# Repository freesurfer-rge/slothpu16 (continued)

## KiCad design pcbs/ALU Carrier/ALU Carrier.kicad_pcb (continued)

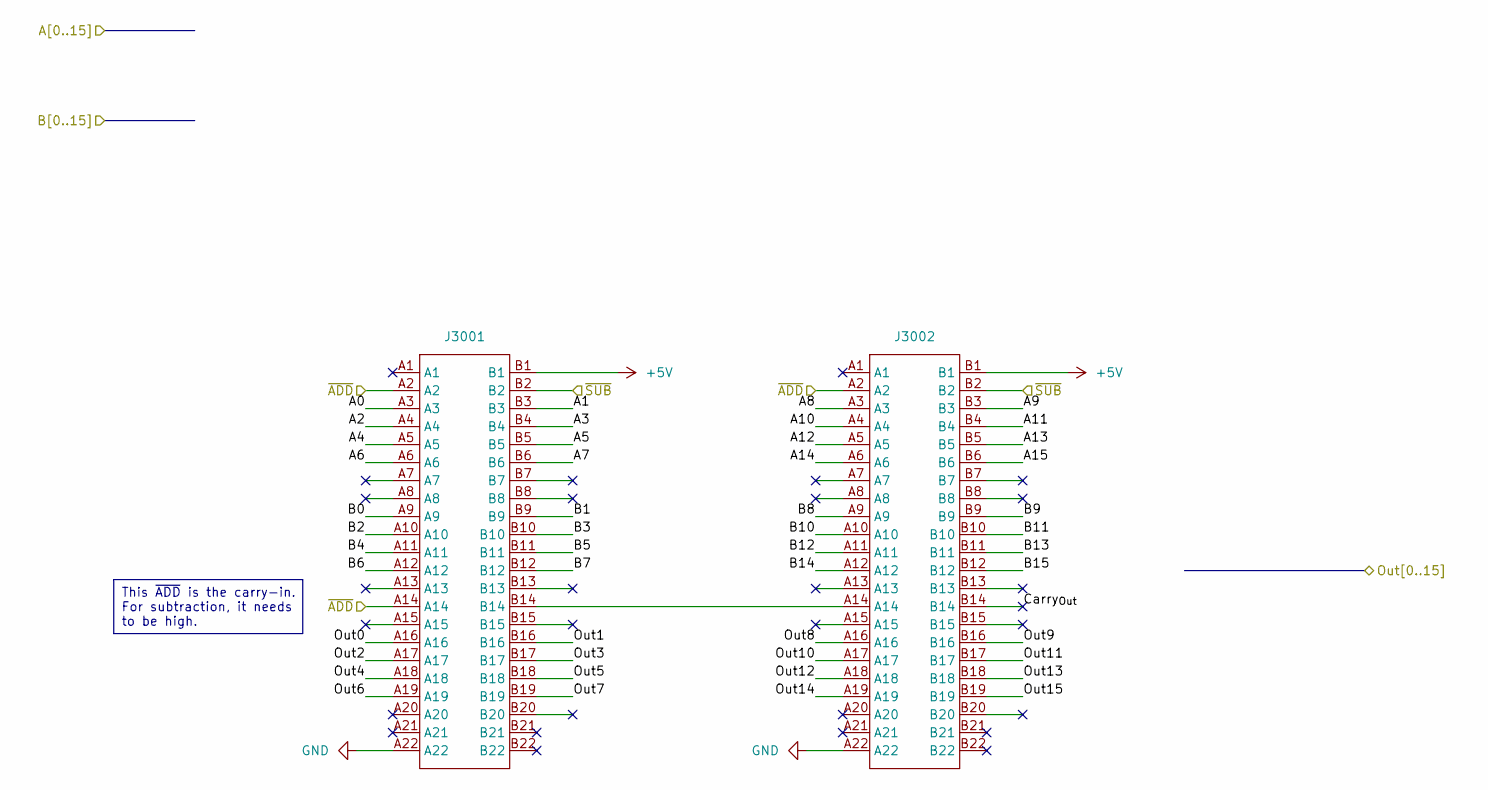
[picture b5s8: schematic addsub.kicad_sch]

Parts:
J3001, J3002: TE-5530843-4-Mount

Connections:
+5V: J3001.B1, J3002.B1; also elsewhere on the board
/A0: J3001.A3; also elsewhere on the board
/A1: J3001.B3; also elsewhere on the board
/A2: J3001.A4; also elsewhere on the board
/A3: J3001.B4; also elsewhere on the board
/A4: J3001.A5; also elsewhere on the board
/A5: J3001.B5; also elsewhere on the board
/A6: J3001.A6; also elsewhere on the board
/A7: J3001.B6; also elsewhere on the board
/A8: J3002.A3; also elsewhere on the board
/A9: J3002.B3; also elsewhere on the board
/A10: J3002.A4; also elsewhere on the board
/A11: J3002.B4; also elsewhere on the board
/A12: J3002.A5; also elsewhere on the board
/A13: J3002.B5; also elsewhere on the board
/A14: J3002.A6; also elsewhere on the board
/A15: J3002.B6; also elsewhere on the board
/Adder Subtractor/Carry_{Out}: J3002.B14
/Adder Subtractor/Out0: J3001.A16; also elsewhere on the board
/Adder Subtractor/Out1: J3001.B16; also elsewhere on the board
/Adder Subtractor/Out2: J3001.A17; also elsewhere on the board
/Adder Subtractor/Out3: J3001.B17; also elsewhere on the board
/Adder Subtractor/Out4: J3001.A18; also elsewhere on the board
/Adder Subtractor/Out5: J3001.B18; also elsewhere on the board
/Adder Subtractor/Out6: J3001.A19; also elsewhere on the board
/Adder Subtractor/Out7: J3001.B19; also elsewhere on the board
/Adder Subtractor/Out8: J3002.A16; also elsewhere on the board
/Adder Subtractor/Out9: J3002.B16; also elsewhere on the board
/Adder Subtractor/Out10: J3002.A17; also elsewhere on the board
/Adder Subtractor/Out11: J3002.B17; also elsewhere on the board
/Adder Subtractor/Out12: J3002.A18; also elsewhere on the board
/Adder Subtractor/Out13: J3002.B18; also elsewhere on the board
/Adder Subtractor/Out14: J3002.A19; also elsewhere on the board
/Adder Subtractor/Out15: J3002.B19; also elsewhere on the board
/Adder Subtractor/~ADD: J3001.A2, J3001.A14, J3002.A2; also elsewhere on the board
/Adder Subtractor/~SUB: J3001.B2, J3002.B2; also elsewhere on the board
/B0: J3001.A9; also elsewhere on the board
/B1: J3001.B9; also elsewhere on the board
/B2: J3001.A10; also elsewhere on the board
/B3: J3001.B10; also elsewhere on the board
/B4: J3001.A11; also elsewhere on the board
/B5: J3001.B11; also elsewhere on the board
/B6: J3001.A12; also elsewhere on the board
/B7: J3001.B12; also elsewhere on the board
/B8: J3002.A9; also elsewhere on the board
/B9: J3002.B9; also elsewhere on the board
/B10: J3002.A10; also elsewhere on the board
/B11: J3002.B10; also elsewhere on the board
/B12: J3002.A11; also elsewhere on the board
/B13: J3002.B11; also elsewhere on the board
/B14: J3002.A12; also elsewhere on the board
/B15: J3002.B12; also elsewhere on the board
GND: J3001.A22, J3002.A22; also elsewhere on the board
unnamed: J3001.B14, J3002.A14

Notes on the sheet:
This ~{ADD} is the carry-in. For subtraction, it needs to be high.

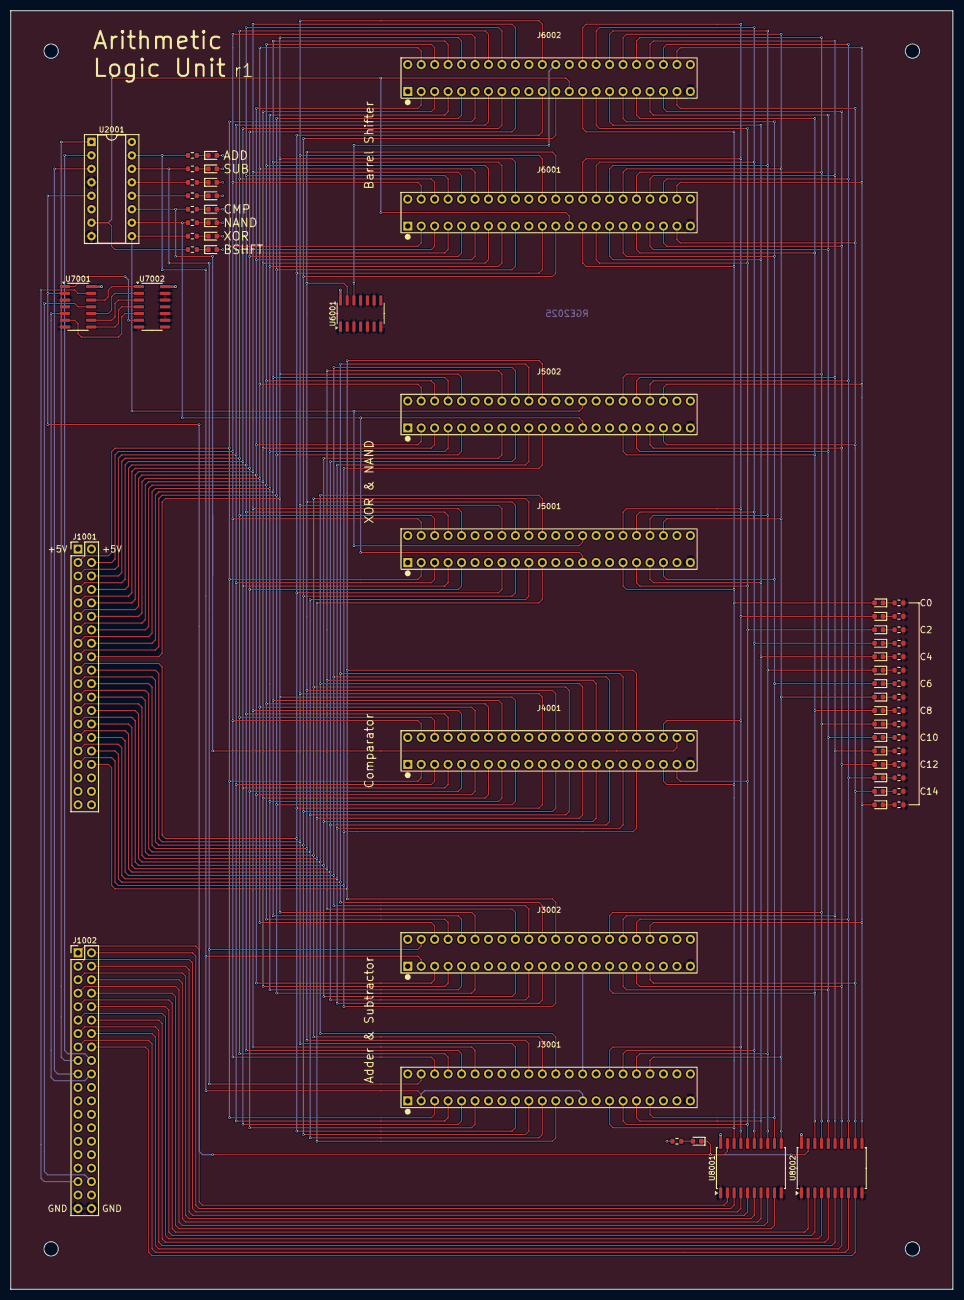
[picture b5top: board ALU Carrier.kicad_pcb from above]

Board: 2 copper layers, 177.8 x 241.3 mm, 69 parts (0 on the bottom side), 114 nets.

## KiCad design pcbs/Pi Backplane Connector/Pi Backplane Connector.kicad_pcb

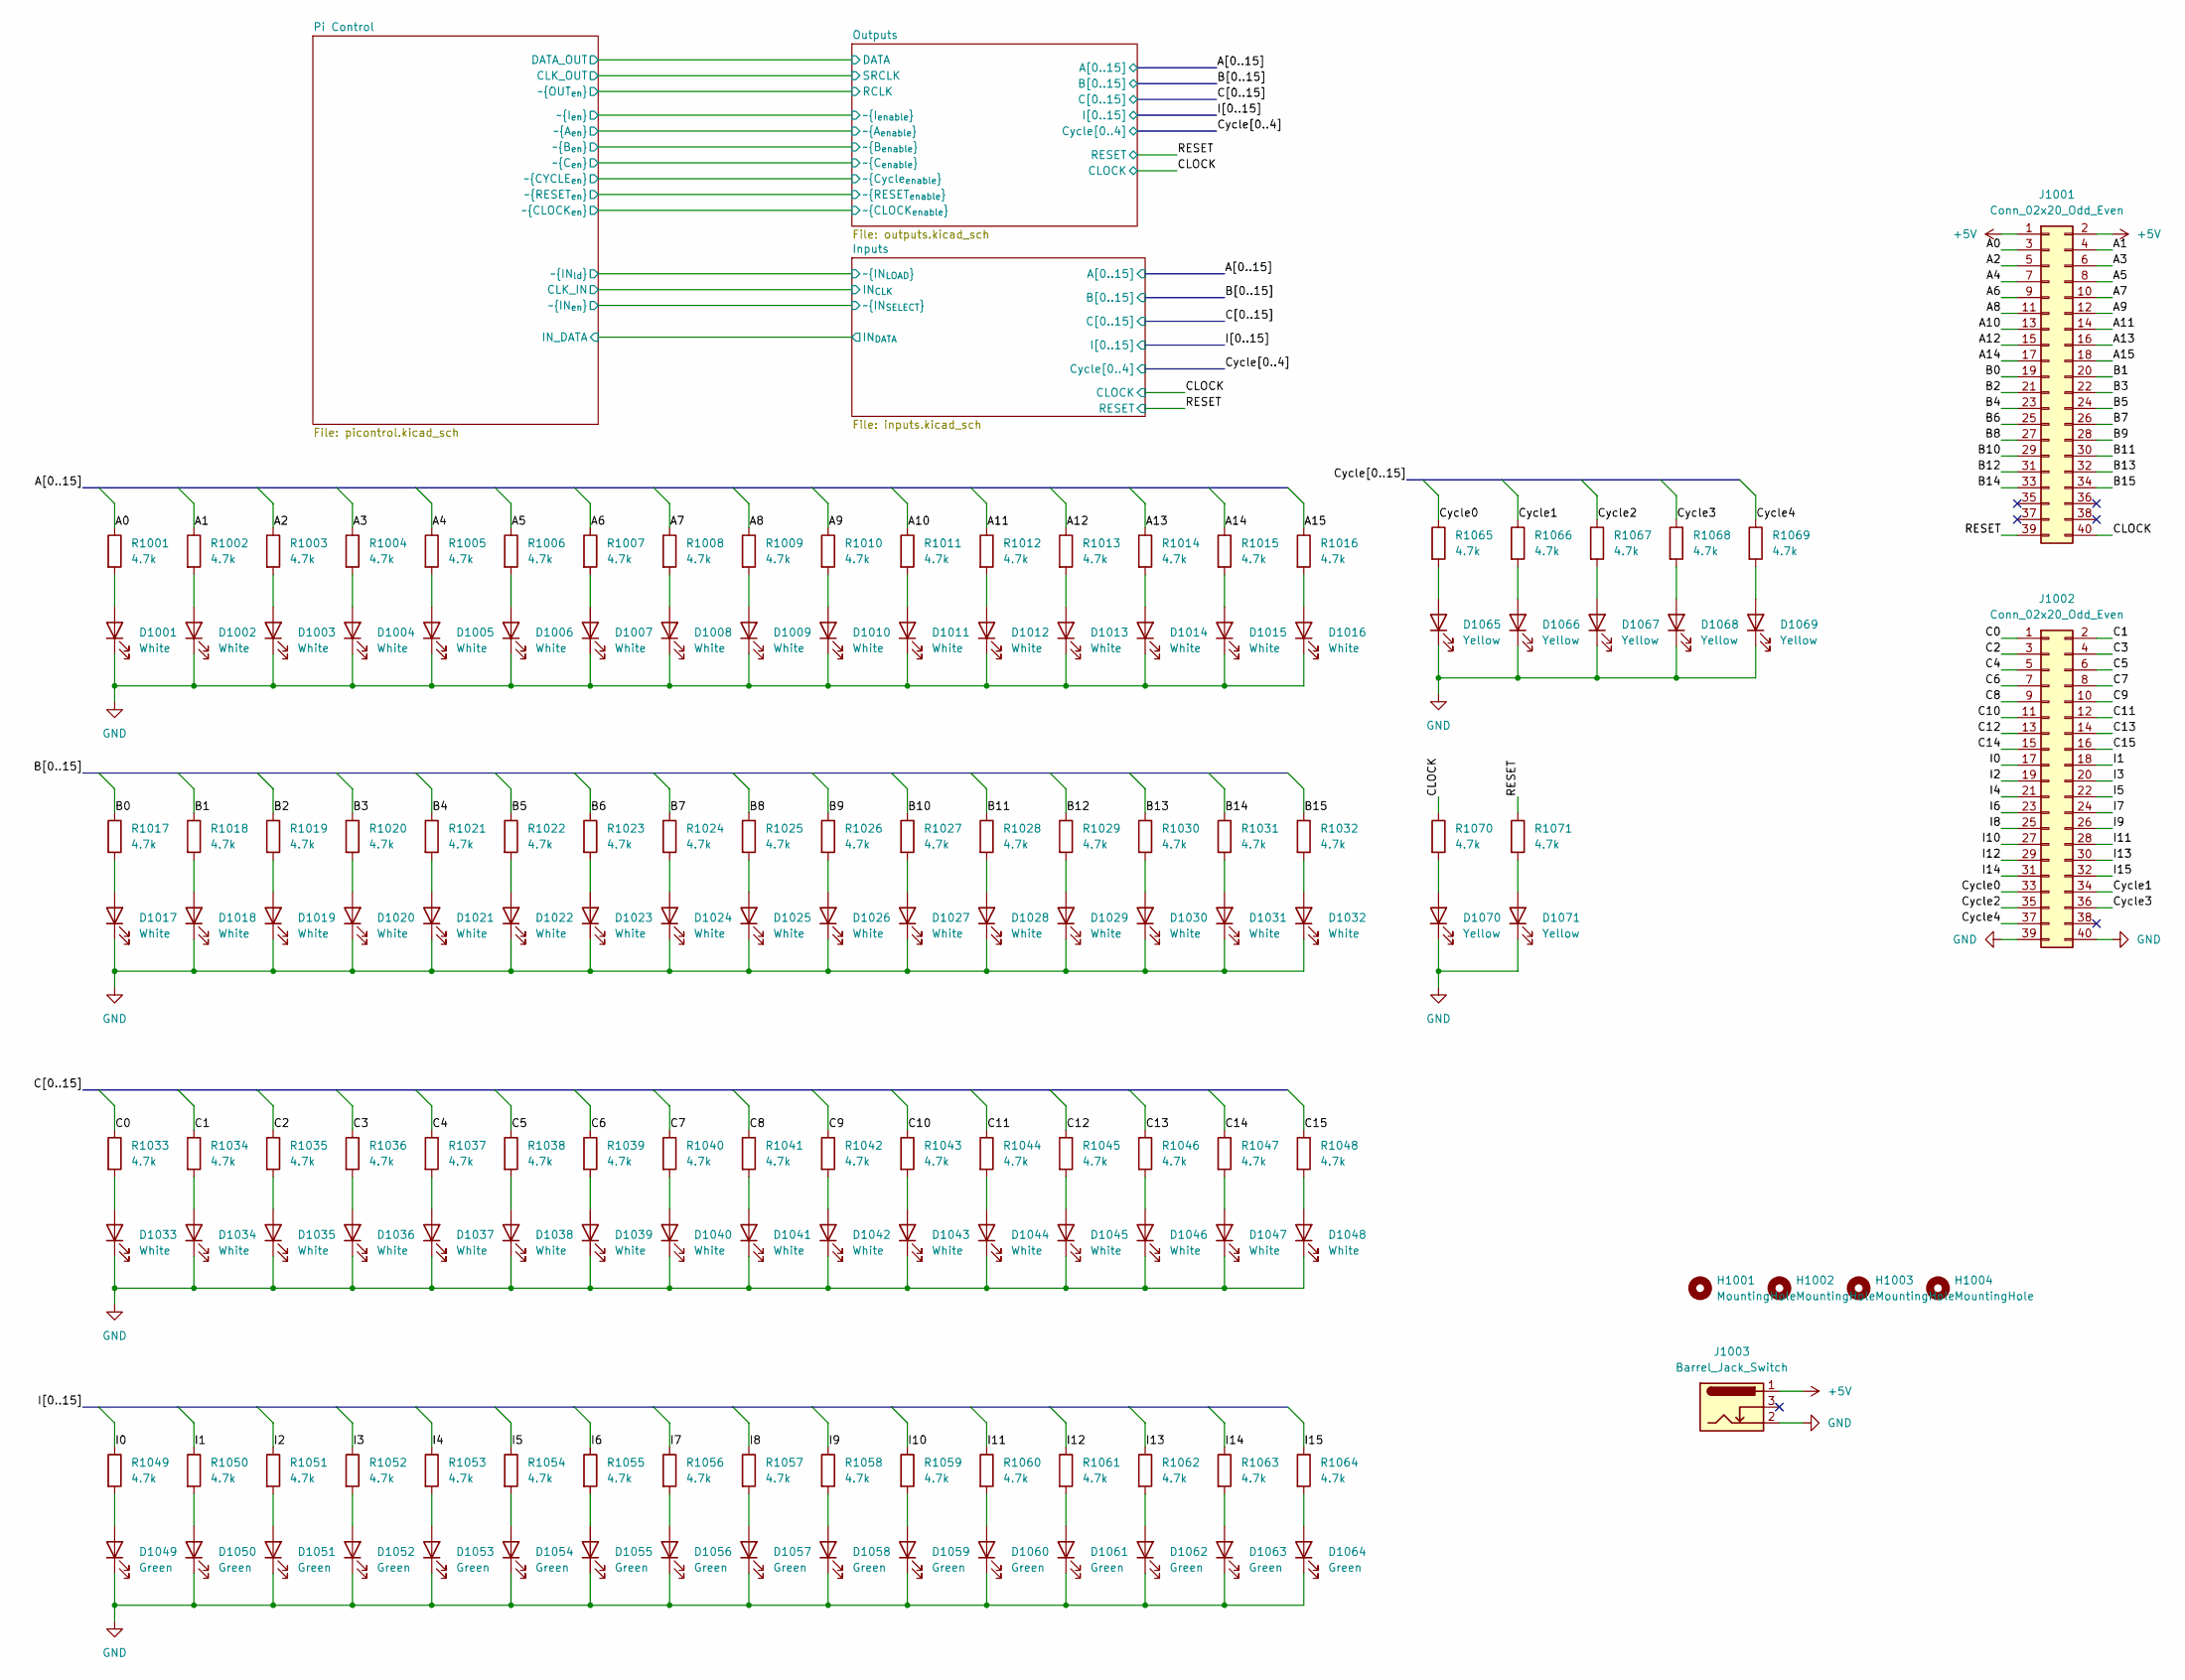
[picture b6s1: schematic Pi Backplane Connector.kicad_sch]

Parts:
D1001, D1002, D1003, D1004, D1005, D1006, D1007, D1008, D1009, D1010, D1011, D1012, D1013, D1014, D1015, D1016, D1017, D1018, D1019, D1020, D1021, D1022, D1023, D1024, D1025, D1026, D1027, D1028, D1029, D1030, D1031, D1032, D1033, D1034, D1035, D1036, D1037, D1038, D1039, D1040, D1041, D1042, D1043, D1044, D1045, D1046, D1047, D1048: White; LED_0603_1608Metric; LCSC C2290
D1049, D1050, D1051, D1052, D1053, D1054, D1055, D1056, D1057, D1058, D1059, D1060, D1061, D1062, D1063, D1064: Green; LED_0603_1608Metric; LCSC C72043
D1065, D1066, D1067, D1068, D1069, D1070, D1071: Yellow; LED_0603_1608Metric; LCSC C72038
H1001, H1002, H1003, H1004: MountingHole; MountingHole_2.7mm_M2.5_ISO7380
J1001, J1002: Conn_02x20_Odd_Even; PinHeader_2x20_P2.54mm_Vertical
J1003: Barrel_Jack_Switch; BarrelJack_Horizontal
R1001, R1002, R1003, R1004, R1005, R1006, R1007, R1008, R1009, R1010, R1011, R1012, R1013, R1014, R1015, R1016, R1017, R1018, R1019, R1020, R1021, R1022, R1023, R1024, R1025, R1026, R1027, R1028, R1029, R1030, R1031, R1032, R1033, R1034, R1035, R1036, R1037, R1038, R1039, R1040, R1041, R1042, R1043, R1044, R1045, R1046, R1047, R1048, R1049, R1050, R1051, R1052, R1053, R1054, R1055, R1056, R1057, R1058, R1059, R1060, R1061, R1062, R1063, R1064, R1065, R1066, R1067, R1068, R1069, R1070, R1071: 4.7k; R_0603_1608Metric; LCSC C23162

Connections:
+5V: J1001.1, J1001.2, J1003.1; also elsewhere on the board
/A0: J1001.3, R1001.1; also elsewhere on the board
/A1: J1001.4, R1002.1; also elsewhere on the board
/A2: J1001.5, R1003.1; also elsewhere on the board
/A3: J1001.6, R1004.1; also elsewhere on the board
/A4: J1001.7, R1005.1; also elsewhere on the board
/A5: J1001.8, R1006.1; also elsewhere on the board
/A6: J1001.9, R1007.1; also elsewhere on the board
/A7: J1001.10, R1008.1; also elsewhere on the board
/A8: J1001.11, R1009.1; also elsewhere on the board
/A9: J1001.12, R1010.1; also elsewhere on the board
/A10: J1001.13, R1011.1; also elsewhere on the board
/A11: J1001.14, R1012.1; also elsewhere on the board
/A12: J1001.15, R1013.1; also elsewhere on the board
/A13: J1001.16, R1014.1; also elsewhere on the board
/A14: J1001.17, R1015.1; also elsewhere on the board
/A15: J1001.18, R1016.1; also elsewhere on the board
/B0: J1001.19, R1017.1; also elsewhere on the board
/B1: J1001.20, R1018.1; also elsewhere on the board
/B2: J1001.21, R1019.1; also elsewhere on the board
/B3: J1001.22, R1020.1; also elsewhere on the board
/B4: J1001.23, R1021.1; also elsewhere on the board
/B5: J1001.24, R1022.1; also elsewhere on the board
/B6: J1001.25, R1023.1; also elsewhere on the board
/B7: J1001.26, R1024.1; also elsewhere on the board
/B8: J1001.27, R1025.1; also elsewhere on the board
/B9: J1001.28, R1026.1; also elsewhere on the board
/B10: J1001.29, R1027.1; also elsewhere on the board
/B11: J1001.30, R1028.1; also elsewhere on the board
/B12: J1001.31, R1029.1; also elsewhere on the board
/B13: J1001.32, R1030.1; also elsewhere on the board
/B14: J1001.33, R1031.1; also elsewhere on the board
/B15: J1001.34, R1032.1; also elsewhere on the board
/C0: J1002.1, R1033.1; also elsewhere on the board
/C1: J1002.2, R1034.1; also elsewhere on the board
/C2: J1002.3, R1035.1; also elsewhere on the board
/C3: J1002.4, R1036.1; also elsewhere on the board
/C4: J1002.5, R1037.1; also elsewhere on the board
/C5: J1002.6, R1038.1; also elsewhere on the board
/C6: J1002.7, R1039.1; also elsewhere on the board
/C7: J1002.8, R1040.1; also elsewhere on the board
/C8: J1002.9, R1041.1; also elsewhere on the board
/C9: J1002.10, R1042.1; also elsewhere on the board
/C10: J1002.11, R1043.1; also elsewhere on the board
/C11: J1002.12, R1044.1; also elsewhere on the board
/C12: J1002.13, R1045.1; also elsewhere on the board
/C13: J1002.14, R1046.1; also elsewhere on the board
/C14: J1002.15, R1047.1; also elsewhere on the board
/C15: J1002.16, R1048.1; also elsewhere on the board
/CLOCK: J1001.40, R1070.1; also elsewhere on the board
/Cycle0: J1002.33, R1065.1; also elsewhere on the board
/Cycle1: J1002.34, R1066.1; also elsewhere on the board
/Cycle2: J1002.35, R1067.1; also elsewhere on the board
/Cycle3: J1002.36, R1068.1; also elsewhere on the board
/Cycle4: J1002.37, R1069.1; also elsewhere on the board
/I0: J1002.17, R1049.1; also elsewhere on the board
/I1: J1002.18, R1050.1; also elsewhere on the board
/I2: J1002.19, R1051.1; also elsewhere on the board
/I3: J1002.20, R1052.1; also elsewhere on the board
/I4: J1002.21, R1053.1; also elsewhere on the board
/I5: J1002.22, R1054.1; also elsewhere on the board
/I6: J1002.23, R1055.1; also elsewhere on the board
/I7: J1002.24, R1056.1; also elsewhere on the board
/I8: J1002.25, R1057.1; also elsewhere on the board
/I9: J1002.26, R1058.1; also elsewhere on the board
/I10: J1002.27, R1059.1; also elsewhere on the board
/I11: J1002.28, R1060.1; also elsewhere on the board
/I12: J1002.29, R1061.1; also elsewhere on the board
/I13: J1002.30, R1062.1; also elsewhere on the board
/I14: J1002.31, R1063.1; also elsewhere on the board
/I15: J1002.32, R1064.1; also elsewhere on the board
/RESET: J1001.39, R1071.1; also elsewhere on the board
GND: D1001.1 (K), D1002.1 (K), D1003.1 (K), D1004.1 (K), D1005.1 (K), D1006.1 (K), D1007.1 (K), D1008.1 (K), D1009.1 (K), D1010.1 (K), D1011.1 (K), D1012.1 (K), D1013.1 (K), D1014.1 (K), D1015.1 (K), D1016.1 (K), D1017.1 (K), D1018.1 (K), D1019.1 (K), D1020.1 (K), D1021.1 (K), D1022.1 (K), D1023.1 (K), D1024.1 (K), D1025.1 (K), D1026.1 (K), D1027.1 (K), D1028.1 (K), D1029.1 (K), D1030.1 (K), D1031.1 (K), D1032.1 (K), D1033.1 (K), D1034.1 (K), D1035.1 (K), D1036.1 (K), D1037.1 (K), D1038.1 (K), D1039.1 (K), D1040.1 (K), D1041.1 (K), D1042.1 (K), D1043.1 (K), D1044.1 (K), D1045.1 (K), D1046.1 (K), D1047.1 (K), D1048.1 (K), D1049.1 (K), D1050.1 (K), D1051.1 (K), D1052.1 (K), D1053.1 (K), D1054.1 (K), D1055.1 (K), D1056.1 (K), D1057.1 (K), D1058.1 (K), D1059.1 (K), D1060.1 (K), D1061.1 (K), D1062.1 (K), D1063.1 (K), D1064.1 (K), D1065.1 (K), D1066.1 (K), D1067.1 (K), D1068.1 (K), D1069.1 (K), D1070.1 (K), D1071.1 (K), J1002.39, J1002.40, J1003.2; also elsewhere on the board
unnamed: D1001.2 (A), R1001.2
unnamed: D1002.2 (A), R1002.2
unnamed: D1003.2 (A), R1003.2
unnamed: D1004.2 (A), R1004.2
unnamed: D1005.2 (A), R1005.2
unnamed: D1006.2 (A), R1006.2
unnamed: D1007.2 (A), R1007.2
unnamed: D1008.2 (A), R1008.2
unnamed: D1009.2 (A), R1009.2
unnamed: D1010.2 (A), R1010.2
unnamed: D1011.2 (A), R1011.2
unnamed: D1012.2 (A), R1012.2
unnamed: D1013.2 (A), R1013.2
unnamed: D1014.2 (A), R1014.2
unnamed: D1015.2 (A), R1015.2
unnamed: D1016.2 (A), R1016.2
unnamed: D1017.2 (A), R1017.2
unnamed: D1018.2 (A), R1018.2
unnamed: D1019.2 (A), R1019.2
unnamed: D1020.2 (A), R1020.2
unnamed: D1021.2 (A), R1021.2
unnamed: D1022.2 (A), R1022.2
unnamed: D1023.2 (A), R1023.2
unnamed: D1024.2 (A), R1024.2
unnamed: D1025.2 (A), R1025.2
unnamed: D1026.2 (A), R1026.2
unnamed: D1027.2 (A), R1027.2
unnamed: D1028.2 (A), R1028.2
unnamed: D1029.2 (A), R1029.2
unnamed: D1030.2 (A), R1030.2
unnamed: D1031.2 (A), R1031.2
unnamed: D1032.2 (A), R1032.2
unnamed: D1033.2 (A), R1033.2
unnamed: D1034.2 (A), R1034.2
unnamed: D1035.2 (A), R1035.2
unnamed: D1036.2 (A), R1036.2
unnamed: D1037.2 (A), R1037.2
unnamed: D1038.2 (A), R1038.2
unnamed: D1039.2 (A), R1039.2
unnamed: D1040.2 (A), R1040.2
unnamed: D1041.2 (A), R1041.2
unnamed: D1042.2 (A), R1042.2
unnamed: D1043.2 (A), R1043.2
unnamed: D1044.2 (A), R1044.2
unnamed: D1045.2 (A), R1045.2
unnamed: D1046.2 (A), R1046.2
unnamed: D1047.2 (A), R1047.2
unnamed: D1048.2 (A), R1048.2
unnamed: D1049.2 (A), R1049.2
unnamed: D1050.2 (A), R1050.2
unnamed: D1051.2 (A), R1051.2
unnamed: D1052.2 (A), R1052.2
unnamed: D1053.2 (A), R1053.2
unnamed: D1054.2 (A), R1054.2
unnamed: D1055.2 (A), R1055.2
unnamed: D1056.2 (A), R1056.2
unnamed: D1057.2 (A), R1057.2
unnamed: D1058.2 (A), R1058.2
unnamed: D1059.2 (A), R1059.2
unnamed: D1060.2 (A), R1060.2
unnamed: D1061.2 (A), R1061.2
unnamed: D1062.2 (A), R1062.2
unnamed: D1063.2 (A), R1063.2
unnamed: D1064.2 (A), R1064.2
unnamed: D1065.2 (A), R1065.2
unnamed: D1066.2 (A), R1066.2
unnamed: D1067.2 (A), R1067.2
unnamed: D1068.2 (A), R1068.2
unnamed: D1069.2 (A), R1069.2
unnamed: D1070.2 (A), R1070.2
unnamed: D1071.2 (A), R1071.2

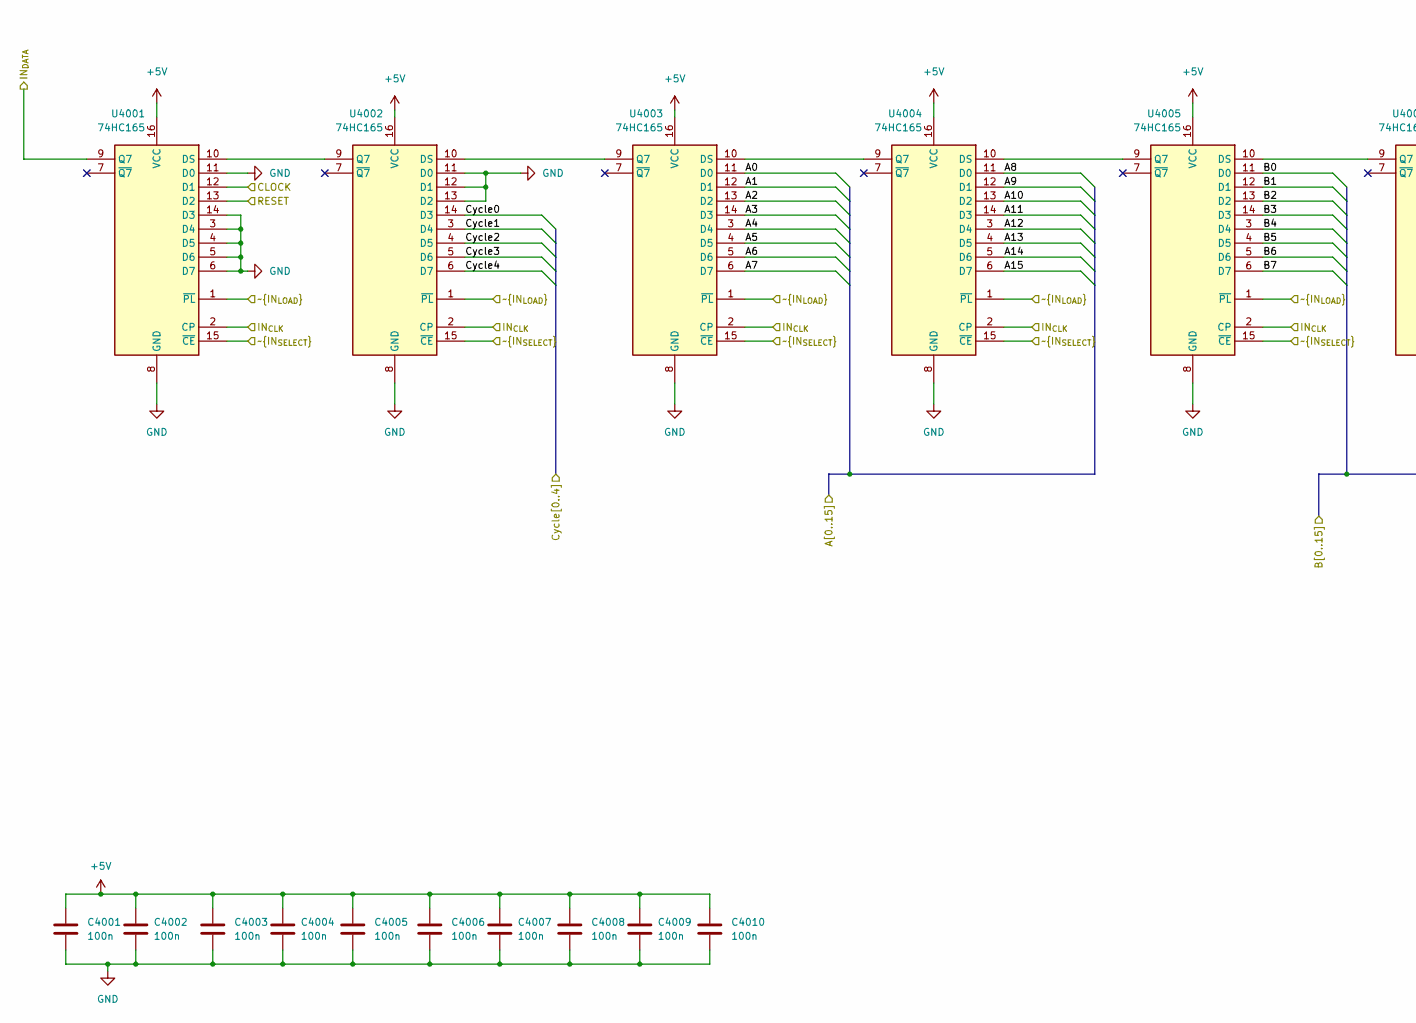
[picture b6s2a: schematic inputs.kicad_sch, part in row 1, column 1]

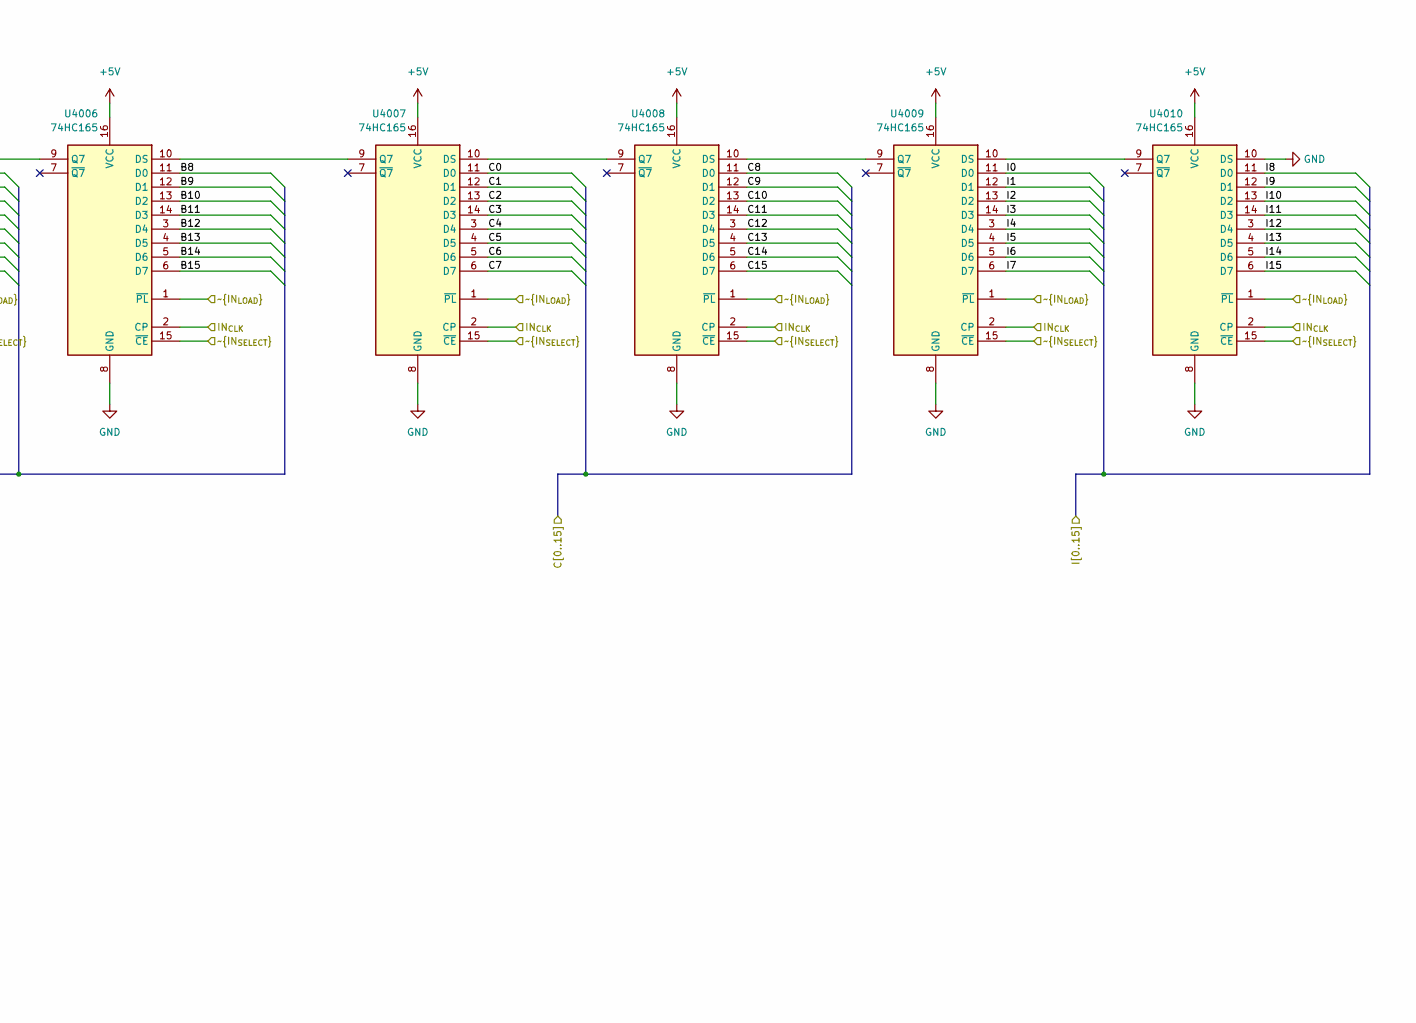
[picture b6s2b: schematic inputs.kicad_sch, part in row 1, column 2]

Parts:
C4001, C4002, C4003, C4004, C4005, C4006, C4007, C4008, C4009, C4010: 100n; C_0603_1608Metric; LCSC C14663
U4001, U4002, U4003, U4004, U4005, U4006, U4007, U4008, U4009, U4010: 74HC165; SOIC-16_3.9x9.9mm_P1.27mm; LCSC C5613

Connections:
+5V: C4001.2, C4002.2, C4003.2, C4004.2, C4005.2, C4006.2, C4007.2, C4008.2, C4009.2, C4010.2, U4001.16 (VCC), U4002.16 (VCC), U4003.16 (VCC), U4004.16 (VCC), U4005.16 (VCC), U4006.16 (VCC), U4007.16 (VCC), U4008.16 (VCC), U4009.16 (VCC), U4010.16 (VCC); also elsewhere on the board
/A0: U4003.11 (D0); also elsewhere on the board
/A1: U4003.12 (D1); also elsewhere on the board
/A2: U4003.13 (D2); also elsewhere on the board
/A3: U4003.14 (D3); also elsewhere on the board
/A4: U4003.3 (D4); also elsewhere on the board
/A5: U4003.4 (D5); also elsewhere on the board
/A6: U4003.5 (D6); also elsewhere on the board
/A7: U4003.6 (D7); also elsewhere on the board
/A8: U4004.11 (D0); also elsewhere on the board
/A9: U4004.12 (D1); also elsewhere on the board
/A10: U4004.13 (D2); also elsewhere on the board
/A11: U4004.14 (D3); also elsewhere on the board
/A12: U4004.3 (D4); also elsewhere on the board
/A13: U4004.4 (D5); also elsewhere on the board
/A14: U4004.5 (D6); also elsewhere on the board
/A15: U4004.6 (D7); also elsewhere on the board
/B0: U4005.11 (D0); also elsewhere on the board
/B1: U4005.12 (D1); also elsewhere on the board
/B2: U4005.13 (D2); also elsewhere on the board
/B3: U4005.14 (D3); also elsewhere on the board
/B4: U4005.3 (D4); also elsewhere on the board
/B5: U4005.4 (D5); also elsewhere on the board
/B6: U4005.5 (D6); also elsewhere on the board
/B7: U4005.6 (D7); also elsewhere on the board
/B8: U4006.11 (D0); also elsewhere on the board
/B9: U4006.12 (D1); also elsewhere on the board
/B10: U4006.13 (D2); also elsewhere on the board
/B11: U4006.14 (D3); also elsewhere on the board
/B12: U4006.3 (D4); also elsewhere on the board
/B13: U4006.4 (D5); also elsewhere on the board
/B14: U4006.5 (D6); also elsewhere on the board
/B15: U4006.6 (D7); also elsewhere on the board
/C0: U4007.11 (D0); also elsewhere on the board
/C1: U4007.12 (D1); also elsewhere on the board
/C2: U4007.13 (D2); also elsewhere on the board
/C3: U4007.14 (D3); also elsewhere on the board
/C4: U4007.3 (D4); also elsewhere on the board
/C5: U4007.4 (D5); also elsewhere on the board
/C6: U4007.5 (D6); also elsewhere on the board
/C7: U4007.6 (D7); also elsewhere on the board
/C8: U4008.11 (D0); also elsewhere on the board
/C9: U4008.12 (D1); also elsewhere on the board
/C10: U4008.13 (D2); also elsewhere on the board
/C11: U4008.14 (D3); also elsewhere on the board
/C12: U4008.3 (D4); also elsewhere on the board
/C13: U4008.4 (D5); also elsewhere on the board
/C14: U4008.5 (D6); also elsewhere on the board
/C15: U4008.6 (D7); also elsewhere on the board
/CLOCK: U4001.12 (D1); also elsewhere on the board
/Cycle0: U4002.14 (D3); also elsewhere on the board
/Cycle1: U4002.3 (D4); also elsewhere on the board
/Cycle2: U4002.4 (D5); also elsewhere on the board
/Cycle3: U4002.5 (D6); also elsewhere on the board
/Cycle4: U4002.6 (D7); also elsewhere on the board
/I0: U4009.11 (D0); also elsewhere on the board
/I1: U4009.12 (D1); also elsewhere on the board
/I2: U4009.13 (D2); also elsewhere on the board
/I3: U4009.14 (D3); also elsewhere on the board
/I4: U4009.3 (D4); also elsewhere on the board
/I5: U4009.4 (D5); also elsewhere on the board
/I6: U4009.5 (D6); also elsewhere on the board
/I7: U4009.6 (D7); also elsewhere on the board
/I8: U4010.11 (D0); also elsewhere on the board
/I9: U4010.12 (D1); also elsewhere on the board
/I10: U4010.13 (D2); also elsewhere on the board
/I11: U4010.14 (D3); also elsewhere on the board
/I12: U4010.3 (D4); also elsewhere on the board
/I13: U4010.4 (D5); also elsewhere on the board
/I14: U4010.5 (D6); also elsewhere on the board
/I15: U4010.6 (D7); also elsewhere on the board
/Inputs/IN_{CLK}: U4001.2 (CP), U4002.2 (CP), U4003.2 (CP), U4004.2 (CP), U4005.2 (CP), U4006.2 (CP), U4007.2 (CP), U4008.2 (CP), U4009.2 (CP), U4010.2 (CP); also elsewhere on the board
/Inputs/IN_{DATA}: U4001.9 (Q7); also elsewhere on the board
/Inputs/~IN_{LOAD}: U4001.1 (~PL), U4002.1 (~PL), U4003.1 (~PL), U4004.1 (~PL), U4005.1 (~PL), U4006.1 (~PL), U4007.1 (~PL), U4008.1 (~PL), U4009.1 (~PL), U4010.1 (~PL); also elsewhere on the board
/Inputs/~IN_{SELECT}: U4001.15 (~CE), U4002.15 (~CE), U4003.15 (~CE), U4004.15 (~CE), U4005.15 (~CE), U4006.15 (~CE), U4007.15 (~CE), U4008.15 (~CE), U4009.15 (~CE), U4010.15 (~CE); also elsewhere on the board
/RESET: U4001.13 (D2); also elsewhere on the board
GND: C4001.1, C4002.1, C4003.1, C4004.1, C4005.1, C4006.1, C4007.1, C4008.1, C4009.1, C4010.1, U4001.3 (D4), U4001.4 (D5), U4001.5 (D6), U4001.6 (D7), U4001.8 (GND), U4001.11 (D0), U4001.14 (D3), U4002.8 (GND), U4002.11 (D0), U4002.12 (D1), U4002.13 (D2), U4003.8 (GND), U4004.8 (GND), U4005.8 (GND), U4006.8 (GND), U4007.8 (GND), U4008.8 (GND), U4009.8 (GND), U4010.8 (GND), U4010.10 (DS); also elsewhere on the board
unnamed: U4001.10 (DS), U4002.9 (Q7)
unnamed: U4002.10 (DS), U4003.9 (Q7)
unnamed: U4003.10 (DS), U4004.9 (Q7)
unnamed: U4004.10 (DS), U4005.9 (Q7)
unnamed: U4005.10 (DS), U4006.9 (Q7)
unnamed: U4006.10 (DS), U4007.9 (Q7)
unnamed: U4007.10 (DS), U4008.9 (Q7)
unnamed: U4008.10 (DS), U4009.9 (Q7)
unnamed: U4009.10 (DS), U4010.9 (Q7)
